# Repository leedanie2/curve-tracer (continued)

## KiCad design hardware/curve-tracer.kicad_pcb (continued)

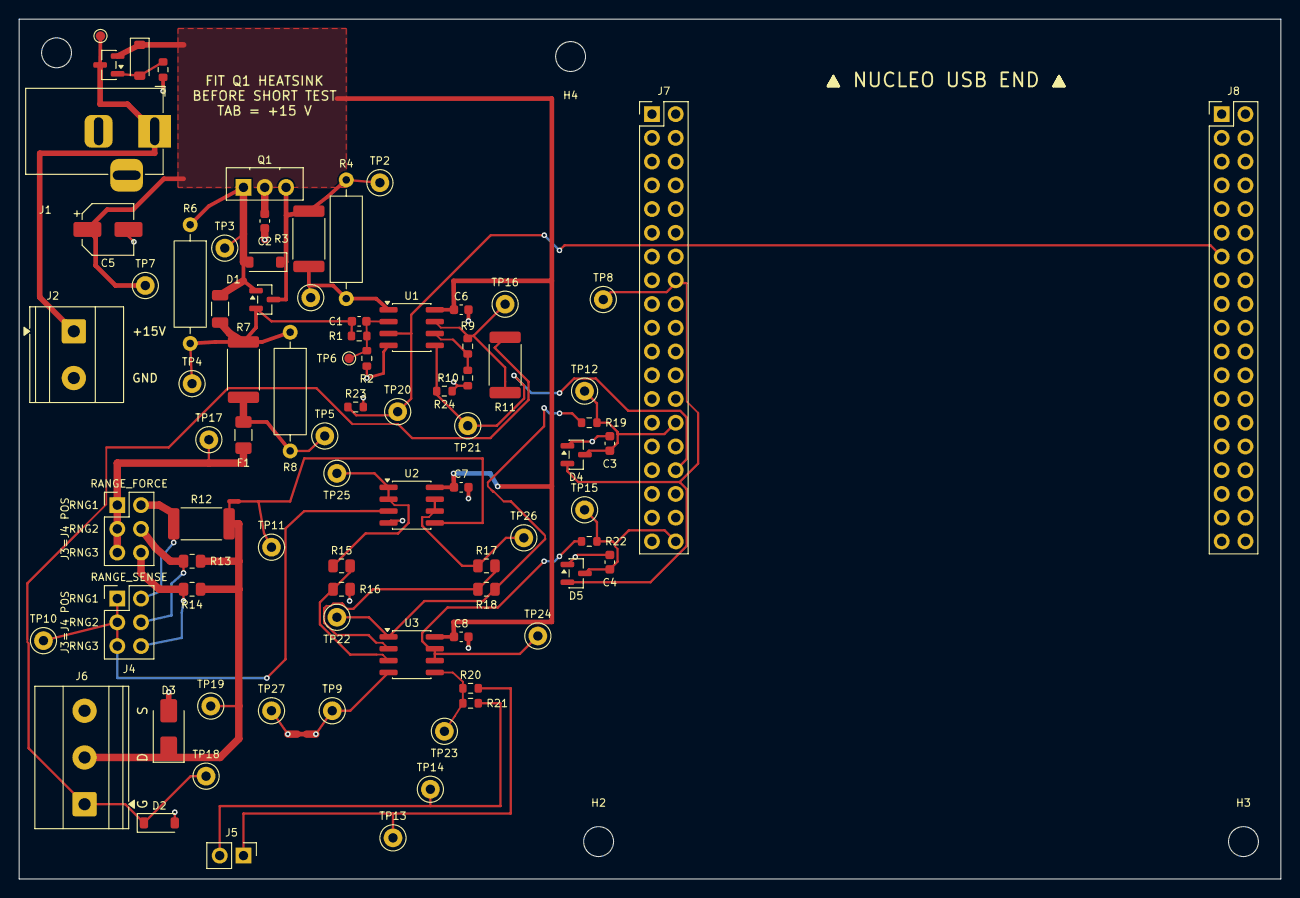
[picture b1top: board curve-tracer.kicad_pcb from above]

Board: 2 copper layers, 135.0 x 92.0 mm, 88 parts (0 on the bottom side), 35 nets.

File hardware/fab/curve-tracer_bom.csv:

"Refs","Value","Footprint","MPN","Manufacturer","LCSC","Assembly","DNP","Qty"
"C1","4.7p C0G","Capacitor_SMD:C_0603_1608Metric","0603CG4R7B500NT","FH (Guangdong Fenghua)","C313086","PCBA","","1"
"C2,C6-C8","100n X7R 50V","Capacitor_SMD:C_0603_1608Metric","CC0603KRX7R9BB104","Yageo","C14663","PCBA","","4"
"C3,C4","10n X7R 50V","Capacitor_SMD:C_0603_1608Metric","0603B103K500NT","FH (Guangdong Fenghua)","C57112","PCBA","","2"
"C5","10u 50V","Capacitor_SMD:CP_Elec_5x5.4","RVT50V10M5X5","jieerrui","C47023118","PCBA","","1"
"D1","1N4148W","Diode_SMD:D_SOD-123","1N4148W","ST(Semtech)","C81598","PCBA","","1"
"D2,D6","BZT52C12 12V","Diode_SMD:D_SOD-123","BZT52C12","MDD(Microdiode Semiconductor)","C173429","PCBA","","2"
"D3","SMAJ12A","Diode_SMD:D_SMA","SMAJ12A","MDD(Microdiode Semiconductor)","C113957","PCBA","","1"
"D4,D5","BAT54S","Package_TO_SOT_SMD:SOT-23","BAT54S","R+O","C7420333","PCBA","","2"
"F1","PTC 100mA hold","Fuse:Fuse_1206_3216Metric","nSMD010","TECHFUSE","C70065","PCBA","","1"
"J1","15V IN","Connector_BarrelJack:BarrelJack_Horizontal","DC-005 2.0","BOOMELE","C16214","PCBA","","1"
"J2","15V BENCH","TerminalBlock_Phoenix:TerminalBlock_Phoenix_MKDS-1,5-2_1x02_P5.00mm_Horizontal","KF301-5.0-2P","Cixi Kefa","C474881","PCBA","","1"
"J3","RANGE_FORCE","curve-tracer:PinHeader_2x03_P2.54mm_Vertical_RangeSelect","PZ254V-12-6P","XFCN","C492420","PCBA","","1"
"J4","RANGE_SENSE","curve-tracer:PinHeader_2x03_P2.54mm_Vertical_RangeSelect","PZ254V-12-6P","XFCN","C492420","PCBA","","1"
"J5","KELVIN  HI / LO","Connector_PinHeader_2.54mm:PinHeader_1x02_P2.54mm_Vertical","PZ254V-11-02P","XFCN","C492401","PCBA","","1"
"J6","DUT  G / D / S","TerminalBlock_Phoenix:TerminalBlock_Phoenix_MKDS-1,5-3_1x03_P5.00mm_Horizontal","KF301-5.0-3P","Cixi Kefa","C474882","PCBA","","1"
"J7","CN7 (morpho)","curve-tracer:PinSocket_2x19_P2.54mm_Vertical_NucleoCarrier","PM254-2-19-Z-8.5","HCTL","C2897420","PCBA","","1"
"J8","CN10 (morpho)","curve-tracer:PinSocket_2x19_P2.54mm_Vertical_NucleoCarrier","PM254-2-19-Z-8.5","HCTL","C2897420","PCBA","","1"
"Q1","BD139","Package_TO_SOT_THT:TO-126-3_Vertical","BD139","STMicroelectronics","C27866","PCBA","","1"
"Q2","MMBT3904","Package_TO_SOT_SMD:SOT-23","MMBT3904","JSCJ","C20526","PCBA","","1"
"Q3","HL2303","Package_TO_SOT_SMD:SOT-23","HL2303","R+O","C7420345","PCBA","","1"
"R1,R9","23.2k 0.1%","Resistor_SMD:R_0603_1608Metric","RT0603BRE0723K2L","Yageo","C861768","PCBA","","2"
"R2,R10","10k 0.1%","Resistor_SMD:R_0603_1608Metric","RT0603BRD0710KL","Yageo","C95204","PCBA","","2"
"R3","330 1% 1W","Resistor_SMD:R_2512_6332Metric","FRC2512F3300TS","FOJAN","C2934068","PCBA","","1"
"R4","330 1% (DNP)","Resistor_THT:R_Axial_DIN0309_L9.0mm_D3.2mm_P12.70mm_Horizontal","","","","DNP","DNP","1"
"R5","10 1%","Resistor_SMD:R_1206_3216Metric","CRCW120610R0FKEAHP","Vishay","C511457","PCBA","","1"
"R6","10 1% (DNP)","Resistor_THT:R_Axial_DIN0309_L9.0mm_D3.2mm_P12.70mm_Horizontal","","","","DNP","DNP","1"
"R7","22 1% 1W","Resistor_SMD:R_2512_6332Metric","RC2512FK-0722RL","Yageo","C276336","PCBA","","1"
"R8","47 1% 1W (DNP)","Resistor_THT:R_Axial_DIN0309_L9.0mm_D3.2mm_P12.70mm_Horizontal","RN1WS47ΩFT/BA1","TyoHM","C385394","DNP","DNP","1"
"R11","1k 1% 1W","Resistor_SMD:R_2512_6332Metric","FRC2512F1001TS","FOJAN","C2960683","PCBA","","1"
"R12","1 1% 1W","Resistor_SMD:R_2512_6332Metric","RC2512FK-071RL","Yageo","C181756","PCBA","","1"
"R13","100 0.1%","Resistor_SMD:R_0805_2012Metric","RT0805BRD07100RL","Yageo","C110773","PCBA","","1"
"R14","10k 0.1%","Resistor_SMD:R_0805_2012Metric","RT0805BRD0710KL","Yageo","C110775","PCBA","","1"
"R15,R17","1k 0.1%","Resistor_SMD:R_0805_2012Metric","RT0805BRD071KL","Yageo","C110774","PCBA","","2"
"R16,R18","20k 0.1%","Resistor_SMD:R_0805_2012Metric","RT0805BRD0720KL","Yageo","C469660","PCBA","","2"
"R19,R22","1k 1%","Resistor_SMD:R_0603_1608Metric","0603WAF1001T5E","UNI-ROYAL","C21190","PCBA","","2"
"R20","300k 0.1%","Resistor_SMD:R_0603_1608Metric","RT0603BRD07300KL","Yageo","C705762","PCBA","","1"
"R21","100k 0.1%","Resistor_SMD:R_0603_1608Metric","RT0603BRD07100KL","Yageo","C122538","PCBA","","1"
"R23,R24","DNP (pull-down)","Resistor_SMD:R_0603_1608Metric","","","","DNP","DNP","2"
"R25","10k 1%","Resistor_SMD:R_0603_1608Metric","0603WAF1002T5E","UNI-ROYAL","C25804","PCBA","","1"
"TP1","OPA_SWEEP_OUT","TestPoint:TestPoint_Keystone_5000-5004_Miniature","RH-5001","ronghe","C5199801","PCBA","","1"
"TP2","BD139_B","TestPoint:TestPoint_Keystone_5000-5004_Miniature","RH-5001","ronghe","C5199801","PCBA","","1"
"TP3","BD139_E","TestPoint:TestPoint_Keystone_5000-5004_Miniature","RH-5001","ronghe","C5199801","PCBA","","1"
"TP4","FB_SENSE","TestPoint:TestPoint_Keystone_5000-5004_Miniature","RH-5001","ronghe","C5199801","PCBA","","1"
"TP5","LOAD","TestPoint:TestPoint_Keystone_5000-5004_Miniature","RH-5001","ronghe","C5199801","PCBA","","1"
"TP7","+15V","TestPoint:TestPoint_Keystone_5000-5004_Miniature","RH-5001","ronghe","C5199801","PCBA","","1"
"TP8","+3V3","TestPoint:TestPoint_Keystone_5000-5004_Miniature","RH-5001","ronghe","C5199801","PCBA","","1"
"TP9","GND_STAR","TestPoint:TestPoint_Keystone_5000-5004_Miniature","RH-5001","ronghe","C5199801","PCBA","","1"
"TP10","SHUNT_HI","TestPoint:TestPoint_Keystone_5000-5004_Miniature","RH-5001","ronghe","C5199801","PCBA","","1"
"TP11","SHUNT_LO","TestPoint:TestPoint_Keystone_5000-5004_Miniature","RH-5001","ronghe","C5199801","PCBA","","1"
"TP12","ADC1_I","TestPoint:TestPoint_Keystone_5000-5004_Miniature","RH-5001","ronghe","C5199801","PCBA","","1"
"TP13","KELVIN_HI","TestPoint:TestPoint_Keystone_5000-5004_Miniature","RH-5001","ronghe","C5199801","PCBA","","1"
"TP14","KELVIN_LO","TestPoint:TestPoint_Keystone_5000-5004_Miniature","RH-5001","ronghe","C5199801","PCBA","","1"
"TP15","ADC2_V","TestPoint:TestPoint_Keystone_5000-5004_Miniature","RH-5001","ronghe","C5199801","PCBA","","1"
"TP16","GATE_AMP","TestPoint:TestPoint_Keystone_5000-5004_Miniature","RH-5001","ronghe","C5199801","PCBA","","1"
"TP17","PTC_OUT","TestPoint:TestPoint_Keystone_5000-5004_Miniature","RH-5001","ronghe","C5199801","PCBA","","1"
"TP18","DUT_G","TestPoint:TestPoint_Keystone_5000-5004_Miniature","RH-5001","ronghe","C5199801","PCBA","","1"
"TP19","DUT_D","TestPoint:TestPoint_Keystone_5000-5004_Miniature","RH-5001","ronghe","C5199801","PCBA","","1"
"TP20","DAC_SWEEP","TestPoint:TestPoint_Keystone_5000-5004_Miniature","RH-5001","ronghe","C5199801","PCBA","","1"
"TP21","DAC_GATE","TestPoint:TestPoint_Keystone_5000-5004_Miniature","RH-5001","ronghe","C5199801","PCBA","","1"
"TP22","DA_OUT","TestPoint:TestPoint_Keystone_5000-5004_Miniature","RH-5001","ronghe","C5199801","PCBA","","1"
"TP23","VDIV","TestPoint:TestPoint_Keystone_5000-5004_Miniature","RH-5001","ronghe","C5199801","PCBA","","1"
"TP24","KBUF_OUT","TestPoint:TestPoint_Keystone_5000-5004_Miniature","RH-5001","ronghe","C5199801","PCBA","","1"
"TP25","BUF_HI","TestPoint:TestPoint_Keystone_5000-5004_Miniature","RH-5001","ronghe","C5199801","PCBA","","1"
"TP26","BUF_LO","TestPoint:TestPoint_Keystone_5000-5004_Miniature","RH-5001","ronghe","C5199801","PCBA","","1"
"TP27","GNDPWR","TestPoint:TestPoint_Keystone_5000-5004_Miniature","RH-5001","ronghe","C5199801","PCBA","","1"
"U1-U3","OPA2197IDR","Package_SO:SOIC-8_3.9x4.9mm_P1.27mm","OPA2197IDR","Texas Instruments","C139363","PCBA","","3"

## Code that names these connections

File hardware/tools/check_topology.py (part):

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    chk(f'one op-amp output per net {shared or ""}', not shared)

    # §3.1 sweep source
    chk('DAC_SWEEP reaches PA6 (CN10-13), shunted to PA5 = DAC1_OUT2 on the Nucleo',
        ('J8', '13') in nl.nets.get('DAC_SWEEP', []))
    chk('R_f (R1) FB_SENSE-IN-, R_g (R2) IN- to GND',
        between('R1', 'FB_SENSE', 'OPA_SWEEP_IN-') and between('R2', 'OPA_SWEEP_IN-', 'GND'))
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            {on(alt, 1), on(alt, 2)} == {on(main, 1), on(main, 2)})

    # §3.2 gate, §3.6 gate protection
    chk('DAC_GATE reaches PA4 (CN7-32)', ('J7', '32') in nl.nets.get('DAC_GATE', []))
    g2 = 1 + val('R9') / val('R10')
    chk(f'gate gain = {g2:.4f}, same as sweep (§3.2)',
        between('R9', 'GATE_AMP', 'GATE_IN-') and between('R10', 'GATE_IN-', 'GND') and g2 == g)
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    chk('Kelvin header J5: 1=KELVIN_HI 2=KELVIN_LO', on('J5', 1) == 'KELVIN_HI' and on('J5', 2) == 'KELVIN_LO')

    # §3.5 ADC pins, §3.7 isolation
    for adc, src, r, c, d, pin in (('ADC1_I', 'DA_OUT', 'R19', 'C3', 'D4', '28'),
                                   ('ADC2_V', 'KBUF_OUT', 'R22', 'C4', 'D5', '38')):
        chk(f'{adc}: {src} through {r} = 1 kΩ (§3.5, §3.7) to CN7-{pin}, 10 nF and BAT54S at the pin',
            between(r, src, adc) and val(r) == 1000 and ('J7', pin) in nl.nets.get(adc, [])
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    # Output clamp (DECISIONS.md D3), fitted since 2026-10-11. Unidirectional:
    # reversed, it is forward-biased by every positive sweep point and holds
    # the DUT node near 0.7 V with the limiter's full current through it.
    chk('D3 SMAJ12A TVS: cathode (pin 1) on DUT_D, anode on GNDPWR, fitted (PCBA)',
        on('D3', 1) == 'DUT_D' and on('D3', 2) == 'GNDPWR'
        and nl.comps['D3']['value'] == 'SMAJ12A'
        and nl.comps['D3']['fields'].get('Assembly') == 'PCBA')
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    ('B-E clamp reversed', [('D1', 2, 'BD139_B'), ('D1', 1, 'BD139_E')]),
    ('difference amp inputs swapped', [('U3', 3, 'DA_N'), ('U3', 2, 'DA_P')]),
    ('Kelvin sense jumper wired to the wrong shunt', [('J4', 2, 'SH2_TOP')]),
    ('ADC1 wired to PA1 instead of PA0', [('J7', 28, 'unconnected-x'), ('J7', 30, 'ADC1_I')]),
    ('Kelvin divider back to 30k/10k: firmware rdiv no longer matches', [('R20', None, '30k 0.1%'), ('R21', None, '10k 0.1%')]),
    ('ADC isolation back to 51 ohm', [('R19', None, '51 1%')]),
    ('stock (mirrored) socket footprint on the Nucleo', [('J7', 'fp', 'Connector_PinSocket_2.54mm:PinSocket_2x19_P2.54mm_Vertical')]),
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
